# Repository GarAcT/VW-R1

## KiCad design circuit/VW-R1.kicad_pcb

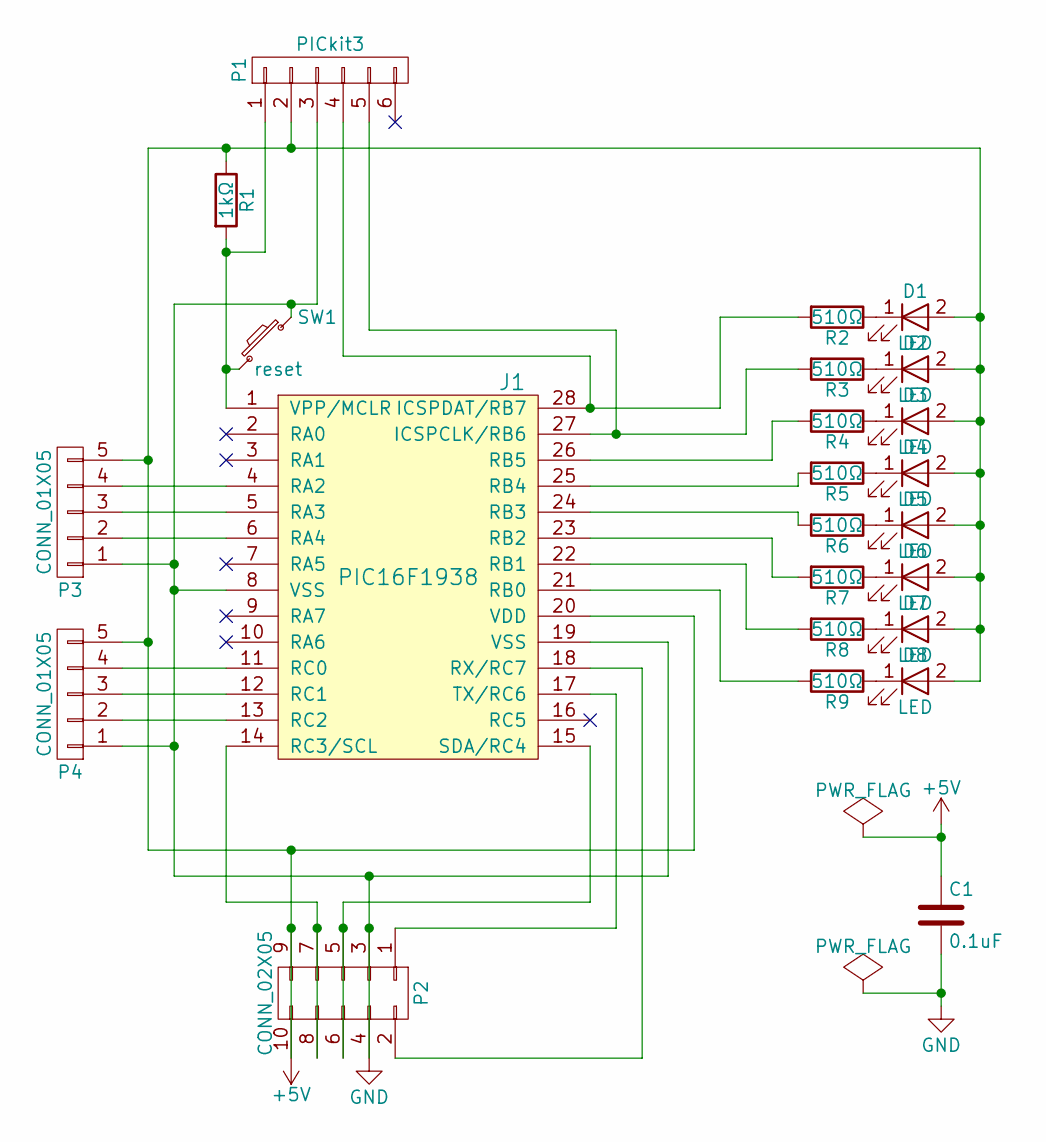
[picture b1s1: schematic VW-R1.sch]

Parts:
C1: 0.1uF; C_Disc_D3_P2.5
D1, D2, D3, D4, D5, D6, D7, D8: LED
J1: PIC16F1938; DIP-28_W7.62mm
P1: PICkit3; Pin_Header_Angled_1x06
P2: CONN_02X05; Pin_Header_Angled_2x05
P3, P4: CONN_01X05; Pin_Header_Angled_1x05
R1: 1kΩ; Resistor_Vertical
R2, R3, R4, R5, R6, R7, R8, R9: 510Ω; Resistor_Vertical
SW1: reset; SW_PUSH_6mmを2.54mmピッチに無理やり押し込んだやつ

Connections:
+5V: C1.1, D1.2 (A), D2.2 (A), D3.2 (A), D4.2 (A), D5.2 (A), D6.2 (A), D7.2 (A), D8.2 (A), J1.20 (VDD), P1.2, P2.9, P2.10, P3.5, P4.5, R1.1
GND: C1.2, J1.8 (VSS), J1.19 (VSS), P1.3, P2.3, P2.4, P3.1, P4.1, SW1.1
unnamed: D1.1 (K), R2.1
unnamed: D2.1 (K), R3.1
unnamed: D3.1 (K), R4.1
unnamed: D4.1 (K), R5.1
unnamed: D5.1 (K), R6.1
unnamed: D6.1 (K), R7.1
unnamed: D7.1 (K), R8.1
unnamed: D8.1 (K), R9.1
unnamed: J1.1 (VPP/MCLR), P1.1, R1.2, SW1.2
unnamed: J1.4 (RA2), P3.4
unnamed: J1.5 (RA3), P3.3
unnamed: J1.6 (RA4), P3.2
unnamed: J1.11 (RC0), P4.4
unnamed: J1.12 (RC1), P4.3
unnamed: J1.13 (RC2), P4.2
unnamed: J1.14 (RC3/SCL), P2.7, P2.8
unnamed: J1.15 (SDA/RC4), P2.5, P2.6
unnamed: J1.17 (TX/RC6), P2.1
unnamed: J1.18 (RX/RC7), P2.2
unnamed: J1.21 (RB0), R9.2
unnamed: J1.22 (RB1), R8.2
unnamed: J1.23 (RB2), R7.2
unnamed: J1.24 (RB3), R6.2
unnamed: J1.25 (RB4), R5.2
unnamed: J1.26 (RB5), R4.2
unnamed: J1.27 (ICSPCLK/RB6), P1.5, R3.2
unnamed: J1.28 (ICSPDAT/RB7), P1.4, R2.2

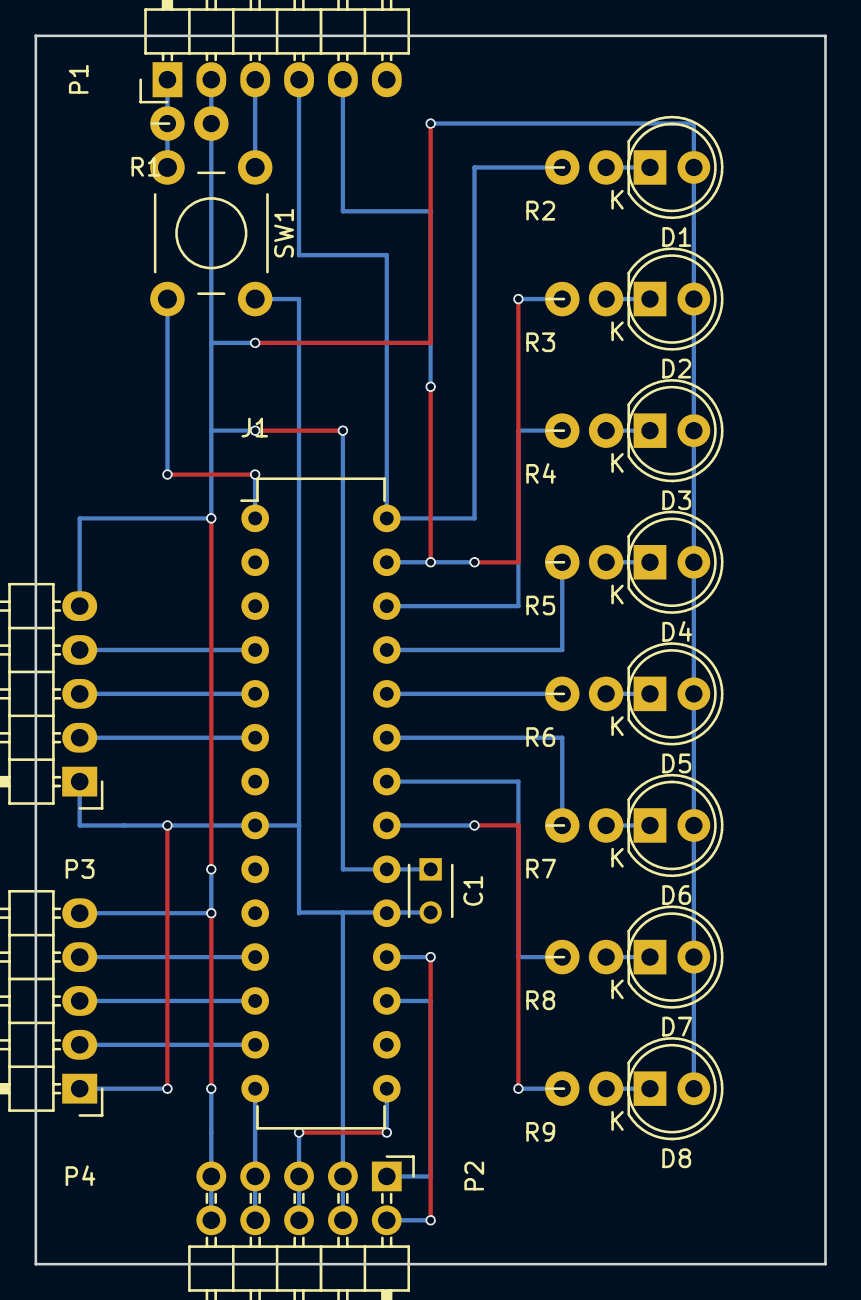
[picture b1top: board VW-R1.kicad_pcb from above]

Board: 2 copper layers, 45.7 x 71.1 mm, 24 parts (0 on the bottom side), 29 nets.

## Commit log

2017-04-08 [hotfix] .gitignoreとKiCadのライブラリを修正
    giboから生成した.gitignoreの中で、C言語の*.libを無視していたのがKiCadのライブラリまで無視されていたのを修正し、不足していたライブラリを追加。
2017-04-08 [add] いろいろできるようにコネクタを追加
    5ピンコネクタx2.
    ・5V/RA3/RA4/RA5/GND
    ・5V/RC0/RC1/RC2/GND
2017-04-20 [fix] コネクタ周りの配線を修正
    追加したコネクタにNHなどの大きめのものを使うと部品と配線が干渉してしまう設計ミスを修正
